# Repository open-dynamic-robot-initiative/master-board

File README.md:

# master-board
Hardware and Firmware of the Solo Quadruped Master Board.

This board centralises all the sensor and actuator data and provides wired and wireless connection to a realtime computer.

Connectivity:

* SPI: Address up to 8 SPI Slave: (max 80Mhz, DMA capable) compatible with BLMC µDriver SPI interface
* Wifi: Wireless communication with a computer via raw ESP-NOW: round trip time of 1.2ms (including driver and OS latency) for a 127bytes message.
* Ethernet: Wired communication with a computer via raw frames: round trip time of 0.2ms (including driver and OS latency) for a 127bytes message.
* GPIO: 4GPIO free. Can be mapped to I2C, UART etc.. Two of them are curently used for IMU communication via UART
* UART: Used to upgrade the ESP32 firmware, free on normal operation.

The board is programed via the ESP-IDF tool chain https://github.com/espressif/esp-idf

Wireless closed loop control at 1kHz demo (click to see video):

IMU, ethernet closed loop cntrol at 1kHz demo (click to see video):

## LED status
**Red fade:** Waiting for init<br>
**Magenta fade:** SPI Autodetect<br>
**Blue fade:** waiting for first commmand<br>
**Green fade:** Active control<br>
**Yellow blink:** ethernet link down state awaiting for link up<br>
**Red blink:** error state (communication with PC), awaiting for new init msg<br>
**White blink:** state machine error (should never happen)<br>

Documentation
-------------
Here are some helpful links to the documentation :

[How to Flash the Master Board (install esp-idf and flash the firmware)](firmware/README.md)

[SDK : How to Prepare Your Interface and Run the Example](sdk/master_board_sdk/README.md)

[Master Board State Machine Description](documentation/masterboard_state_machine.md)

[Description of the Communication Between the Master Board and the Computer](documentation/masterboard_communication.md)

[Description of the BLMC µDriver SPI Interface](documentation/BLMC_%C2%B5Driver_SPI_interface.md)

[Wiring the Master Board](documentation/masterboard_wiring.md)

[Master Board Ordering and Preparation](documentation/masterboard_ordering_soldering.md)

Authors
--------
Thomas Flayols  
Etienne Arlaud

License
-------
BSD 2-Clause License

Copyright
-----------
Copyright (c) 2019, LAAS-CNRS, Max Planck Gesellschaft, New York University

More Information
----------------
[Open Dynamic Robot Initiative](https://open-dynamic-robot-initiative.github.io)

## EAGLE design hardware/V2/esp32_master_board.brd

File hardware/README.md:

The hardware CAD file of the master-board has been created with Eagle.

# Version 1.0 (legacy)
The version 1.0 include an esp32 with GPIO connectors, 8 multiplexed SPI lines, A 5-60V to 3.3V regulator and a Ethernet PHY.
This version suffer from some limitations:
 * The 300ma current limitation of the voltage regulator is easely reach. 
 * The decoupling cappacitor could be increased.
 * The 1st pin label of DEMUX footprint is wrong
 
# Vesrion 2.0 (Latest stable version)
Chage log:
 * Add a RGB LED to ease the feedback while developping.
 * make a dedicated IMU connector
 * Switch to a more capable 3.3V voltage regulator (1A) to power 3DM-CX5-25 IMU

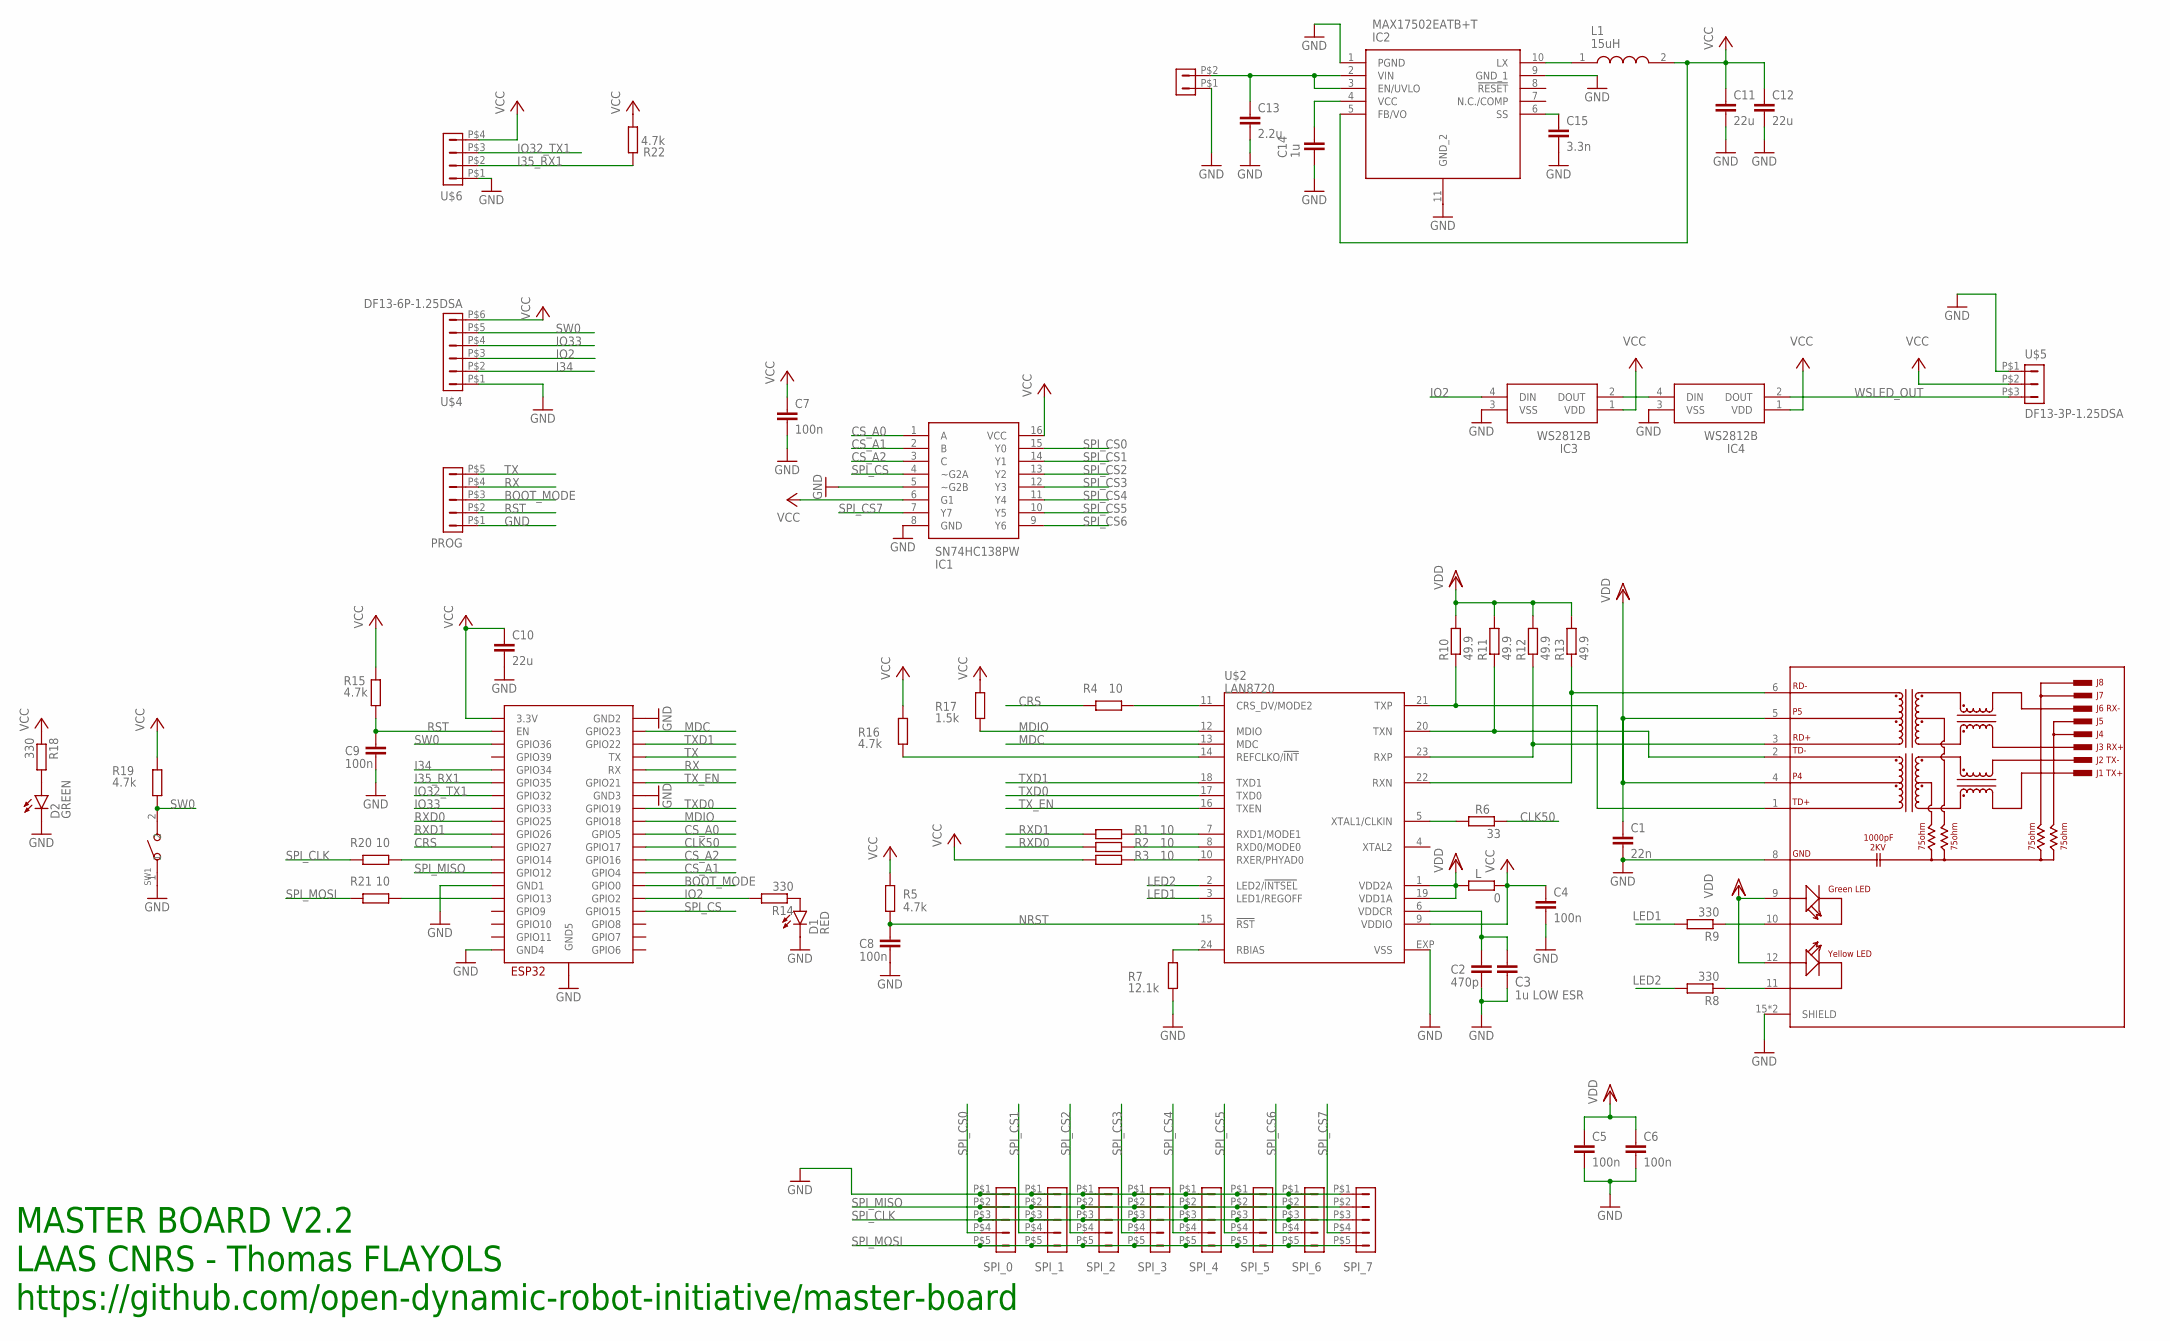
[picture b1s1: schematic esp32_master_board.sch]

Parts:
C1: 22n; 0402; MANUFACTURER_PART_NUMBER 885012205052
C2: 470p; 0402; MANUFACTURER_PART_NUMBER CL05C471JB5NNNC
C3: 1u LOW ESR; 0402; MANUFACTURER_PART_NUMBER CPL-CAP-X5R-0402-1UF-6.3V
C4, C5, C6, C7, C8, C9: 100n; 0402; MANUFACTURER_PART_NUMBER CPL-CAP-X7R-0402-100NF-16V
C10, C11, C12: 22u; C0805; MANUFACTURER_PART_NUMBER CPL-CAP-X5R-0805-22UF-6.3V
C13: 2.2u; C1210; MANUFACTURER_PART_NUMBER C3225X7R1H225K250AB
C14: 1u; 0402; MANUFACTURER_PART_NUMBER CPL-CAP-X5R-0402-1UF-6.3V
C15: 3.3n; 0402; MANUFACTURER_PART_NUMBER 885012205064
D1: RED; CHIPLED_0603; MANUFACTURER_PART_NUMBER CPL-LED-0603-RED
D2: GREEN; CHIPLED_0603; MANUFACTURER_PART_NUMBER CPL-LED-0603-GREEN
IC1: SN74HC138PW; SOP65P640X120-16N
IC2: MAX17502EATB+T; SON50P200X300X80-11N
IC3, IC4: WS2812B
L: 0; 0402; MANUFACTURER_PART_NUMBER CPL-RES-0402-0-0.063W
L1: 15uH; LPS6235
POWER: DF13-2P-1.25DSA; MANUFACTURER_PART_NUMBER DF13-3P-1.25DSA
PROG: DF13-5P-1.25DSA; MANUFACTURER_PART_NUMBER DF13-5P-1.25DSA
R1, R2, R3, R4, R20, R21: 10; 0402; MANUFACTURER_PART_NUMBER CPL-RES-0402-10-0.063W
R5, R15, R16, R19, R22: 4.7k; 0402; MANUFACTURER_PART_NUMBER CPL-RES-0402-4.7K-0.063W
R6: 33; 0402; MANUFACTURER_PART_NUMBER CRCW040233R0FKEDC
R7: 12.1k; 0402; MANUFACTURER_PART_NUMBER ERJ-U02F1212X
R8, R9, R14, R18: 330; 0402; MANUFACTURER_PART_NUMBER RC0402JR-13330RL
R10, R11, R12, R13: 49.9; 0402; MANUFACTURER_PART_NUMBER CRCW040249R9FKEDC
R17: 1.5k; 0402; MANUFACTURER_PART_NUMBER ERJ2GEJ152X
SPI_0, SPI_1, SPI_2, SPI_3, SPI_4, SPI_5, SPI_6, SPI_7: DF13-5P-1.25DSA; MANUFACTURER_PART_NUMBER DF13-5P-1.25DSA
SW1: B3U-1000P-2P-SMD; SW2-2.6-3.0X2.5X1.2+0.4MM; MANUFACTURER_PART_NUMBER B3U-1000P
U$1: ESP32-WROOM; MANUFACTURER_PART_NUMBER ESP32-WROOM-32D
U$2: LAN8720; QFN24; MANUFACTURER_PART_NUMBER LAN8720A-CP
U$3: HR911105A; HANRUN_HR911105A; MANUFACTURER_PART_NUMBER HR911105A
U$4: DF13-6P-1.25DSA; MANUFACTURER_PART_NUMBER DF13-6P-1.25DSA
U$5: DF13-3P-1.25DSA; MANUFACTURER_PART_NUMBER DF13-3P-1.25DSA
U$6: DF13-4P-1.25DSA; MANUFACTURER_PART_NUMBER DF13-4P-1.25DSA

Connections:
BOOT_MODE: PROG.P$3 (3), U$1.IO0 (GPIO0)
CLK50: R6.1, U$1.IO17 (GPIO17)
CRS: R4.1, U$1.IO27 (GPIO27)
CS_A0: IC1.1 (A), U$1.IO5 (GPIO5)
CS_A1: IC1.2 (B), U$1.IO4 (GPIO4)
CS_A2: IC1.3 (C), U$1.IO16 (GPIO16)
GND: C1.2, C2.2, C3.2, C4.2, C5.2, C6.2, C7.2, C8.2, C9.2, C10.2, C11.2, C12.2, C13.2, C14.1, C15.2, D1.C, D2.C, IC1.5 (~G2B), IC1.8 (GND), IC2.1 (PGND), IC2.9 (GND_1), IC2.11 (GND_2), IC3.3 (VSS), IC4.3 (VSS), POWER.P$1 (1), PROG.P$1 (1), R7.1, SPI_0.P$1 (1), SPI_1.P$1 (1), SPI_2.P$1 (1), SPI_3.P$1 (1), SPI_4.P$1 (1), SPI_5.P$1 (1), SPI_6.P$1 (1), SPI_7.P$1 (1), SW1.1, U$1.GND1, U$1.GND2, U$1.GND3, U$1.GND4, U$1.GND5, U$2.EXP (VSS), U$3.8 (GND), U$3.15 (SHIELD), U$3.16 (SHIELD), U$4.P$1 (1), U$5.P$1 (1), U$6.P$1 (1)
I34: U$1.IO34 (GPIO34), U$4.P$2 (2)
I35_RX1: R22.2, U$1.IO35 (GPIO35), U$6.P$2 (2)
IO2: IC3.4 (DIN), R14.2, U$1.IO2 (GPIO2), U$4.P$3 (3)
IO32_TX1: U$1.IO32 (GPIO32), U$6.P$3 (3)
IO33: U$1.IO33 (GPIO33), U$4.P$4 (4)
LED1: R9.2, U$2.3 (LED1/REGOFF)
LED2: R8.2, U$2.2 (LED2/!INTSEL)
MDC: U$1.IO23 (GPIO23), U$2.13 (MDC)
MDIO: R17.1, U$1.IO18 (GPIO18), U$2.12 (MDIO)
unnamed: R1.2, U$2.7 (RXD1/MODE1)
unnamed: R2.2, U$2.8 (RXD0/MODE0)
unnamed: R3.2, U$2.10 (RXER/PHYAD0)
unnamed: R4.2, U$2.11 (CRS_DV/MODE2)
unnamed: R6.2, U$2.5 (XTAL1/CLKIN)
unnamed: R7.2, U$2.24 (RBIAS)
unnamed: R10.1, U$2.21 (TXP), U$3.1 (TD+)
unnamed: R11.1, U$2.20 (TXN), U$3.2 (TD-)
unnamed: R12.1, U$2.23 (RXP), U$3.3 (RD+)
unnamed: R13.1, U$2.22 (RXN), U$3.6 (RD-)
unnamed: R8.1, U$3.11 (YC)
unnamed: R9.1, U$3.10 (GC)
unnamed: R16.1, U$2.14 (REFCLKO/!INT)
unnamed: C2.1, C3.1, U$2.6 (VDDCR)
unnamed: C14.2, IC2.4 (VCC)
unnamed: D1.A, R14.1
unnamed: R21.2, U$1.IO13 (GPIO13)
unnamed: IC2.10 (LX), L1.1
unnamed: IC3.2 (DOUT), IC4.4 (DIN)
unnamed: D2.A, R18.2
unnamed: R20.2, U$1.IO14 (GPIO14)
unnamed: C15.1, IC2.6 (SS)
unnamed: C13.1, IC2.2 (VIN), IC2.3 (EN/UVLO), POWER.P$2 (2)
NRST: C8.1, R5.1, U$2.15 (!RST)
RST: C9.1, PROG.P$2 (2), R15.1, U$1.EN
RX: PROG.P$4 (4), U$1.RX
RXD0: R2.1, U$1.IO25 (GPIO25)
RXD1: R1.1, U$1.IO26 (GPIO26)
SPI_CLK: R20.1, SPI_0.P$3 (3), SPI_1.P$3 (3), SPI_2.P$3 (3), SPI_3.P$3 (3), SPI_4.P$3 (3), SPI_5.P$3 (3), SPI_6.P$3 (3), SPI_7.P$3 (3)
SPI_CS: IC1.4 (~G2A), U$1.IO15 (GPIO15)
SPI_CS0: IC1.15 (Y0), SPI_0.P$4 (4)
SPI_CS1: IC1.14 (Y1), SPI_1.P$4 (4)
SPI_CS2: IC1.13 (Y2), SPI_2.P$4 (4)
SPI_CS3: IC1.12 (Y3), SPI_3.P$4 (4)
SPI_CS4: IC1.11 (Y4), SPI_4.P$4 (4)
SPI_CS5: IC1.10 (Y5), SPI_5.P$4 (4)
SPI_CS6: IC1.9 (Y6), SPI_6.P$4 (4)
SPI_CS7: IC1.7 (Y7), SPI_7.P$4 (4)
SPI_MISO: SPI_0.P$2 (2), SPI_1.P$2 (2), SPI_2.P$2 (2), SPI_3.P$2 (2), SPI_4.P$2 (2), SPI_5.P$2 (2), SPI_6.P$2 (2), SPI_7.P$2 (2), U$1.IO12 (GPIO12)
SPI_MOSI: R21.1, SPI_0.P$5 (5), SPI_1.P$5 (5), SPI_2.P$5 (5), SPI_3.P$5 (5), SPI_4.P$5 (5), SPI_5.P$5 (5), SPI_6.P$5 (5), SPI_7.P$5 (5)
SW0: R19.1, SW1.2, U$1.SENSOR_VP (GPIO36), U$4.P$5 (5)
TX: PROG.P$5 (5), U$1.TX
TXD0: U$1.IO19 (GPIO19), U$2.17 (TXD0)
TXD1: U$1.IO22 (GPIO22), U$2.18 (TXD1)
TX_EN: U$1.IO21 (GPIO21), U$2.16 (TXEN)
VCC: C4.1, C7.1, C10.1, C11.1, C12.1, IC1.6 (G1), IC1.16 (VCC), IC2.5 (FB/VO), IC3.1 (VDD), IC4.1 (VDD), L.1, L1.2, R3.1, R5.2, R15.2, R16.2, R17.2, R18.1, R19.2, R22.1, U$1.3V3 (3.3V), U$2.9 (VDDIO), U$4.P$6 (6), U$5.P$2 (2), U$6.P$4 (4)
VDD: C1.1, C5.1, C6.1, L.2, R10.2, R11.2, R12.2, R13.2, U$2.1 (VDD2A), U$2.19 (VDD1A), U$3.4, U$3.5, U$3.9 (GA), U$3.12 (YA)
WSLED_OUT: IC4.2 (DOUT), U$5.P$3 (3)

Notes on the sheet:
MASTER BOARD V2.2 LAAS CNRS - Thomas FLAYOLS https://github.com/open-dynamic-robot-initiative/master-board

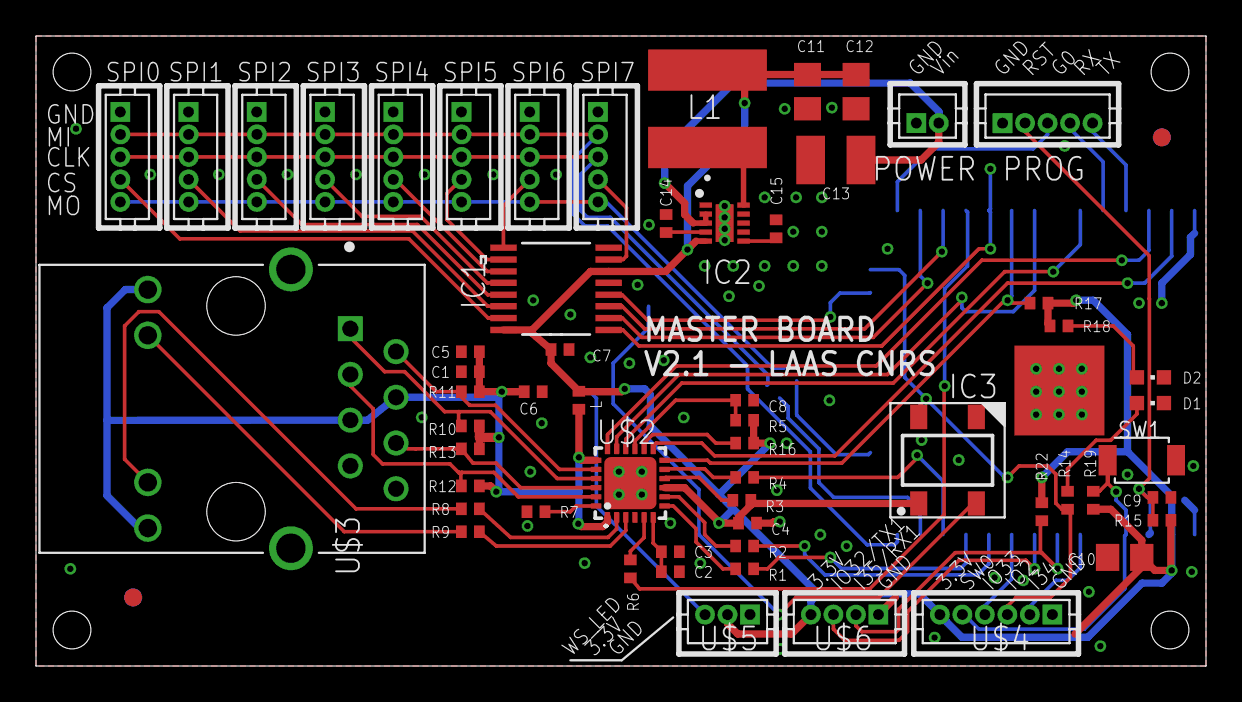
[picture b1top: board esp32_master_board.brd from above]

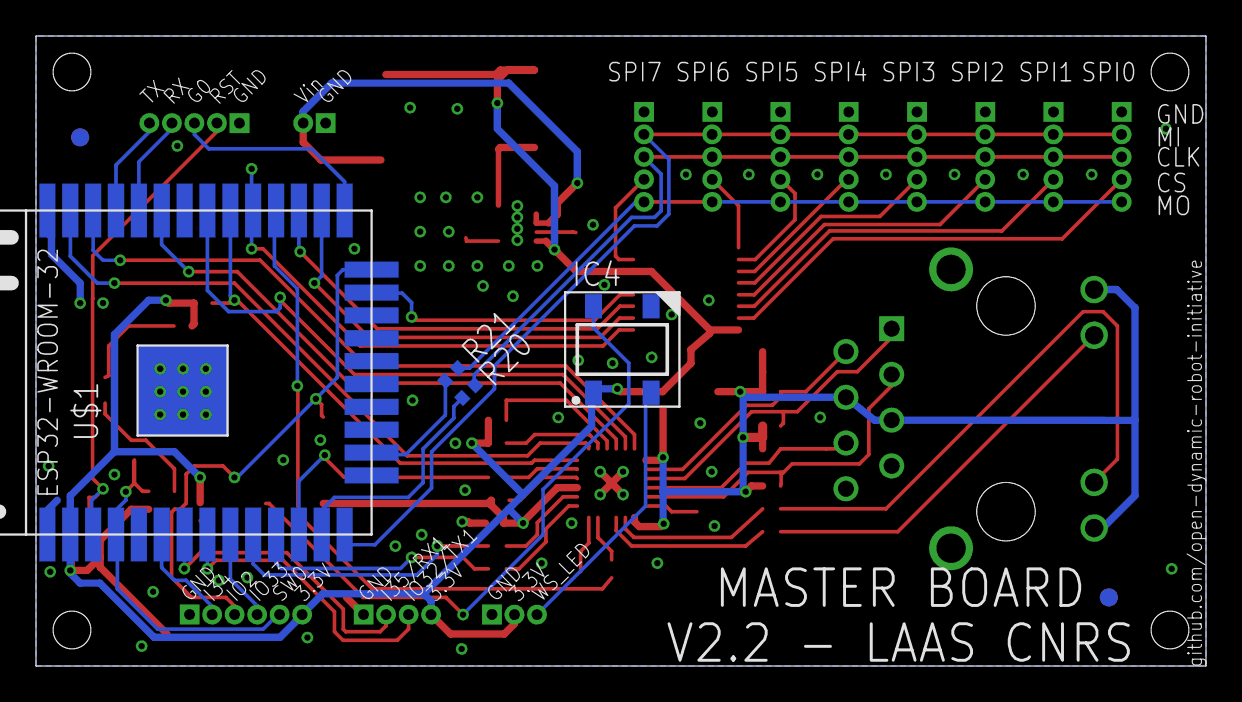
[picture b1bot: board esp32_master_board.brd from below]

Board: 2 copper layers, 65.0 x 35.0 mm, 66 parts (6 on the bottom side), 64 nets.

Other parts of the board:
REF1, REF2, REF3, REF4: VISION_REF10

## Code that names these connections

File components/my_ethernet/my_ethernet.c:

#include "my_ethernet.h"

uint8_t eth_src_mac[6] = {0xb4, 0xe6, 0x2d, 0xb5, 0x9f, 0x88};
uint8_t eth_dst_mac[6] = {0xFF, 0xFF, 0xFF, 0xFF, 0xFF, 0xFF};

void (*eth_recv_cb)(uint8_t src_mac[6], uint8_t *data, int len) = NULL;

static const char* ETH_TAG = "my_ethernet";

static void eth_gpio_config_rmii(void) {
    // RMII data pins are fixed:
    // TXD0 = GPIO19
    // TXD1 = GPIO22
    // TX_EN = GPIO21
    // RXD0 = GPIO25
    // RXD1 = GPIO26
    // CLK == GPIO0
    phy_rmii_configure_data_interface_pins();
    phy_rmii_smi_configure_pins(PIN_SMI_MDC, PIN_SMI_MDIO);
}


static esp_err_t eth_event_handler(void *ctx, system_event_t *event) {
  tcpip_adapter_ip_info_t ipInfo;

  switch(event->event_id) {
    case ETHERNET_EVENT_CONNECTED:
        ESP_LOGI(ETH_TAG, "Ethernet Link Up");
        break;
    case ETHERNET_EVENT_DISCONNECTED:
        ESP_LOGI(ETH_TAG, "Ethernet Link Down");
        break;
    case ETHERNET_EVENT_START:
        ESP_LOGI(ETH_TAG, "Ethernet Started");
        break;
    case ETHERNET_EVENT_STOP:
        ESP_LOGI(ETH_TAG, "Ethernet Stopped");
        break;
    case SYSTEM_EVENT_ETH_GOT_IP:
        ESP_LOGI(ETH_TAG, "Ethernet got IP");
        ESP_ERROR_CHECK(tcpip_adapter_get_ip_info(TCPIP_ADAPTER_IF_ETH, &ipInfo));
        ESP_LOGI(ETH_TAG, "TCP/IP initialization finished.");
        ESP_LOGI(ETH_TAG, "TCP|IP \t IP:"IPSTR, IP2STR(&ipInfo.ip));
        ESP_LOGI(ETH_TAG, "TCP|IP \t MASK:"IPSTR, IP2STR(&ipInfo.netmask));
        ESP_LOGI(ETH_TAG, "TCP|IP \t GW:"IPSTR, IP2STR(&ipInfo.gw));
        xEventGroupSetBits(udp_event_group, WIFI_CONNECTED_BIT);
    default:
      ESP_LOGI(ETH_TAG, "Unhandled Ethernet event (id = %d)", event->event_id);
        break;
    }
  return ESP_OK;
}


static esp_err_t eth_recv_func (void *buffer, uint16_t len, void *eb) {
  eth_frame *frame = buffer;
  if(eth_recv_cb == NULL) {
    ESP_LOGE(ETH_TAG, "Ethernet frame received but no callback function is set on received...");
  } else if(len < sizeof(eth_frame) - CONFIG_MAX_ETH_DATA_LEN) {
    ESP_LOGE(ETH_TAG, "The ethernet frame received is too short : frame length = %dB / minimum length expected (for header) = %dB", len, sizeof(eth_frame) - CONFIG_MAX_ETH_DATA_LEN);
  } else if(len > sizeof(eth_frame)) {
    ESP_LOGE(ETH_TAG, "The ethernet frame received is too long : frame length = %dB / maximum length = %dB", len, sizeof(eth_frame));
  } else if(frame->ethertype != ETHERTYPE) {
    ESP_LOGE(ETH_TAG, "Unexpected frame ethertype : got %d instead of %d", frame->ethertype, ETHERTYPE);
  } else if(frame->data_len > len - sizeof(eth_frame) + CONFIG_MAX_ETH_DATA_LEN) {
    ESP_LOGE(ETH_TAG, "Data longer than available frame length : data length = %d / available frame length = %d", frame->data_len, len - sizeof(eth_frame) + CONFIG_MAX_ETH_DATA_LEN);
  } else {
    eth_recv_cb(frame->dst_mac, frame->data, frame->data_len);
  }
  return ESP_OK;
}


void eth_init_frame(eth_frame *p_frame) {
  p_frame->ethertype = ETHERTYPE;
  memcpy(p_frame->dst_mac, eth_dst_mac, sizeof(uint8_t) * 6);  
  memcpy(p_frame->src_mac, eth_src_mac, sizeof(uint8_t) * 6);
}


esp_err_t eth_send_frame(eth_frame *p_frame)
{
  int err = esp_eth_tx((uint8_t *) p_frame, sizeof(eth_frame) + (p_frame->data_len) - CONFIG_MAX_ETH_DATA_LEN);
  
  if (err < 0) {
    ESP_LOGE(ETH_TAG, "Erromar occurred while sending eth frame: errno %d", errno);
    return ESP_FAIL;
  }

  return ESP_OK;
}


void eth_detach_recv_cb() {
  eth_recv_cb = NULL;
}


void eth_attach_recv_cb(void (*cb)(uint8_t src_mac[6], uint8_t *data, int len)) {
  eth_recv_cb = cb;
}


void eth_init() {
  ////////////////////////////////////
  //EVENT HANDLER (CALLBACK)
  ////////////////////////////////////
    //TCP/IP event handling & group (akin to flags and semaphores)
    udp_event_group = xEventGroupCreate();
    ESP_ERROR_CHECK(esp_event_loop_init(eth_event_handler, NULL) );

  ////////////////////////////////////
  //TCP/IP DRIVER INIT WITH A STATIC IP
  ////////////////////////////////////
    tcpip_adapter_init();
    tcpip_adapter_ip_info_t ipInfo;

    //Stop DHCP
    tcpip_adapter_dhcpc_stop(TCPIP_ADAPTER_IF_ETH);

    //Set the static IP
    ip4addr_aton(DEVICE_IP, &ipInfo.ip);
    ip4addr_aton(DEVICE_GW, &ipInfo.gw);
    ip4addr_aton(DEVICE_NETMASK, &ipInfo.netmask);
    ESP_ERROR_CHECK(tcpip_adapter_set_ip_info(TCPIP_ADAPTER_IF_ETH, &ipInfo));

  ////////////////////////////////////
  //ETHERNET CONFIGURATION & INIT
  ////////////////////////////////////

    eth_config_t config = ETHERNET_PHY_CONFIG;
    config.phy_addr = PHY1;
    config.gpio_config = eth_gpio_config_rmii;
    config.tcpip_input = &eth_recv_func;
    config.clock_mode = CONFIG_PHY_CLOCK_MODE;

    ESP_ERROR_CHECK(esp_eth_init(&config));
    ESP_ERROR_CHECK(esp_eth_enable());

    ESP_LOGI(ETH_TAG, "Establishing connetion...");
    xEventGroupWaitBits(udp_event_group, WIFI_CONNECTED_BIT,true, true, portMAX_DELAY);
    ESP_LOGI(ETH_TAG, "Connected");
}

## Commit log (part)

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2020-03-30 add feedback on packet loss
2020-03-30 Add link to the wiring documentation
2020-04-02 New ethernet lib to work with ESP-IDF v4.0
2020-04-04 New sdkconfig to work with ESP-IDF v4.0 (generated from .defaults)
2020-04-04 Update .gitignore for current sdk location
2020-04-05 Fix wrong variable name
2020-04-07 Remove button handling
2020-04-07 Giving feedback on packet loss
2020-04-07 Handling the case when no link state callback function has been set
2020-04-08 Update master board state diagram image
2020-04-14 Initializing p_trans array to avoid a very rare and specific crash while sending an init msg to the mb
2020-04-14 Small refactor + a few comments
2020-04-15 Reset variables for feedback on packet loss after init
2020-04-15 Lttle fix on copying state in main callback
2020-04-16 Small refactor spi_autodetect state
2020-04-16 Added feedback on number of spi slaves connected in ack msg
2020-04-16 Update documentation for feedback on connected SPI slaves
2020-04-17 Updated documentation with protocol version in init msgs
2020-04-17 Added an error msg to sensor packet when a spi transaction failed
2020-04-17 Better handling of variables when there is a state change
2020-04-17 Added listener mode to the interface that allows to get sensor data from any running mb (no session id checking)
2020-04-20 Added getters for feedback and changed stats print functions
2020-04-21 Initialization of bpf in ESPNOW_manager
2020-04-21 Update doc about session id
2020-04-23 Updated outdated doc
2020-04-28 Added default argument for listener mode in interface constructor
2020-05-04 Close correctly the pthread to avoid memory leaks
2020-05-04 Free link_handler when the program is stopped by SIGINT signal
2020-05-04 Disabled debug prints
2020-05-07 Fix for command loss feedback reset and overflow
2020-05-09 [hardware] V2.1: Add MPN for all parts, fix some footprints, add BOM compatible with seeedfusion PCBA, add pick and place files
2020-05-12 Small trace path changes to prevent possible shorting of MISO line due to sharp grounded ESP32 module corner, small optimisations
2020-05-15 Removed mistakenly added line in default config
2020-05-20 Documentation update : added informations about the latency calculator script
2020-06-11 Improving display of latency test result
2020-06-12 Revert "Changing scheduler param to realtime in examples"
    This reverts commit beead35848bc759a2ef147b0a68dc79b47e57f74.
2020-06-17 Merged PrintCmdStats and PrintSensorStats, improved the display of wifi/eth stats
2020-06-24 Added getters for wifi channel and protocol version
2020-07-06 Update state machine documentation
2020-07-07 Removed wifi channel menuconfig entry and tcpip adpater use
2020-07-07 Fixed wifi deinit and channel change issue
2020-07-15 Small fix for wifi event handlers
2020-07-16 SPI: using polling instead of interrupts
2020-07-16 Placed spi pre and post cbs into IRAM
2020-07-21 Plot graphs even if the script is stopped by a master board timeout
2020-07-31 Temporary fix failing spi transactions in error state
2020-07-31 Update sdkconfig
2020-08-26 Update WS2812b library to remove ambiguity on the part orientation (pin3 indicated by a triangle on the part)
2020-10-07 Tune data representation in the protocol for usefull gains levels, Fix conevrsion of Kp Kd
2020-10-13 CMake: ensure python lib always find c++ lib
2020-11-13 [SDK] Add support for current saturation
2020-11-16 export the cmake library
2020-11-16 Synchronize.
2020-11-16 fix a couple of warnings
2020-11-17 update the interface to double values
2020-12-01 SDK: Adding error code for encoder2 error
2021-01-20 Revert the change for CONFIG_SPI_N_ATTEMPT 3 -> 2
2021-02-24 added led status at readme
2021-04-13 [firmware] update doc
2021-06-25 Set close to zero velocity to zero. Fixes #92
2021-07-13 Fix problem with reference to packed fields in MasterBoardInterface::ParseSensorData
2021-07-21 Add comment to explain the call to ParseSensorData
2021-07-28 update doc including powerboard data in sensor packets
2021-08-02 Implement changes to protocol #4 for the feedforward profile in the SDK and firmware
2021-09-23 pull out more data
2021-10-05 print the histogram and dumpt data all the time
2021-10-18 fix "cannot bind packed field" on Ubuntu 20.04
    While the old version is building on Ubuntu 18.04, newer versions of gcc
    do not allow the assignment to reference here.
2022-01-21 SDK: cherry-pick fixes, fix #106
    initial commit: 32b0252c64a064c55e8cd07115a003b15c0d0a86
2022-03-16 Update README.md
    Fix License according to License file
2022-04-08 Rewrite IMU driver using mailbox, fixing esp32 hardware bug on uart fifo
2022-05-20 Adding example for collecting and plotting IMU data for 10 seconds
2022-05-23 fix example_imu_data_collection
2022-07-19 1. implemented substitution clock() to perf_counter because of python3 don't maintain already it. 2. in line while ((not robot_if.IsTimeout()) and ( (perf_counter() - glob_last) < 20)): created misse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
2022-09-16 Avoid fixed-point overflow
2022-09-19 Increase FLOAT_TO_D32QN &c range
2022-09-20 Check for compatible catch2 version
2022-09-28 Revert "Add error code for SPI CRC error"
    This reverts commit 5d95db4b35e33a5f52f3c232c0c7dbf1ebddd7ec.
2022-09-28 Handle out-of-range motor params without wraparound (#117)
    Avoid fixed-point overflow
2022-12-21 Remove vscode hidden files
2022-12-22 plateform and distro modules optionnal for sdk example com_analyser.py
2023-01-31 fixed typos in firmware README.md
2023-03-08 Zero-initialise all members of Motor
    This should fix an issue that was likely caused by `kp` being set to
    some random non-zero value, resulting in the motor unintentionally being
    held at some position.
2023-03-08 example.py: Initialise all reference values and gains to zero
    This should not really be needed anymore since values are already
    zero-initialised in `Motor` but better be safe than sorry.
2023-03-11 Fix missing header.
2023-04-17 [Link_manager] Fix message when the priority is not set correctly and fails using assert.
2023-04-25 pre-commit
2023-05-26 Add .github/workflows
2023-05-26 [package.xml] XML version 1.0
2023-05-27 [Cmake] remove python components.
2023-05-29 [sdk/master_board_sdk/CMakeLists.txt] Update Find Python detection. Update message when detection is failing.
2023-05-29 [cmake] Change again python detection place.
2023-05-29 [github/workflows/ros-ci.yml] Fix wrong directory.
2023-06-21 [cmake] Add install procedure for file package.xml
2023-06-23 [CMakeLists.txt] Uses ROS-2 if the environment is compatible.
2023-06-23 [master_board_sdk/package.xml] Remove ament_cmake dependency and buildtool dependency.
2023-07-10 Bump ros-industrial/industrial_ci
    Bumps [ros-industrial/industrial_ci](https://github.com/ros-industrial/industrial_ci) from afbf77f39db26785371161d5691ab435b31bb3ba to 9f963f67ebb889792175776c5ee00134d7bb569b.
    - [Commits](https://github.com/ros-industrial/industrial_ci/compare/afbf77f39db26785371161d5691ab435b31bb3ba...9f963f67ebb889792175776c5ee00134d7bb569b)
    ---
    updated-dependencies:
    - dependency-name: ros-industrial/industrial_ci
    dependency-type: direct:production
2023-09-04 Bump actions/checkout from 3 to 4
    Bumps [actions/checkout](https://github.com/actions/checkout) from 3 to 4.
    - [Release notes](https://github.com/actions/checkout/releases)
    - [Changelog](https://github.com/actions/checkout/blob/main/CHANGELOG.md)
    - [Commits](https://github.com/actions/checkout/compare/v3...v4)
    ---
    updated-dependencies:
2023-09-05 [protocol] FLOAT_TO_D8QN has a wrong bracket. This commit fix this.
2023-09-25 CMake: get the submodule if necessary
2023-10-11 Fix git conflicts
2023-11-27 Bump ros-industrial/industrial_ci
    Bumps [ros-industrial/industrial_ci](https://github.com/ros-industrial/industrial_ci) from 9e8b4aaec69f7cade96eda5cfcb3e7da57b99c6e to 3ed9846c96ed1e0bb36193e8e250632eaac980d0.
    - [Commits](https://github.com/ros-industrial/industrial_ci/compare/9e8b4aaec69f7cade96eda5cfcb3e7da57b99c6e...3ed9846c96ed1e0bb36193e8e250632eaac980d0)
    ---
    updated-dependencies:
    - dependency-name: ros-industrial/industrial_ci
    dependency-type: direct:production
2024-01-22 Bump actions/cache from 3 to 4
    Bumps [actions/cache](https://github.com/actions/cache) from 3 to 4.
    - [Release notes](https://github.com/actions/cache/releases)
    - [Changelog](https://github.com/actions/cache/blob/main/RELEASES.md)
    - [Commits](https://github.com/actions/cache/compare/v3...v4)
    ---
    updated-dependencies:
2024-03-31 Add stdexcept as an include in example.cpp Fix https://github.com/open-dynamic-robot-initiative/master-board/issues/153
2024-04-04 Add CV7-AHRS IMU and selection menu
2024-05-04 Add missing stdexcept.
2024-05-17 CMakeLists.txt : don't search for boost.python, let the jrl cmakemodule do the job
2024-06-21 [tests] Add dependency to catch2 for tests in package.xml
2024-06-21 [github/workflows] Renamed correctly the workflows.
2024-06-28 Fix CHANGELOG.md for the given
2024-07-05 CMake: we need to search for boost python if we want to link to it
2025-05-20 Cmake: update submodule
2025-05-21 nix: add flake for sdk package
2025-05-21 ci: checking out the code helps, usually
2025-05-21 nix: preemptively add python312Packages.numpy as runtime dep
2025-05-21 Revert "ci debug why submodules: recursive does nothing"
    This reverts commit 3f6f59a384defbc28bf7bc6c60c076b7fd89eea2.
2025-05-21 ci: enable logs for nix build
2025-05-21 nix: dynamically get ROS version from package.xml
    see https://github.com/Gepetto/nix-lib/pull/1
2025-05-22 ci: enforce flake.lock correctness
2025-05-26 ci: debug missig arg src-*
2025-06-02 nix: fix rosVersion call, add example/ to src fileset
2025-06-03 typo
2025-06-04 ci: run on macos too
2025-06-05 fix formatting blunder
2025-08-19 Bump actions/checkout from 4 to 5
    Bumps [actions/checkout](https://github.com/actions/checkout) from 4 to 5.
    - [Release notes](https://github.com/actions/checkout/releases)
    - [Changelog](https://github.com/actions/checkout/blob/main/CHANGELOG.md)
    - [Commits](https://github.com/actions/checkout/compare/v4...v5)
    ---
    updated-dependencies:
2025-12-15 Bump ros-industrial/industrial_ci
    Bumps [ros-industrial/industrial_ci](https://github.com/ros-industrial/industrial_ci) from eb3ea328ff056aa2435d5b3493e7e2929c310f8e to ba2a3d0f830f8051b356711a8df2fedfc5d256cf.
    - [Commits](https://github.com/ros-industrial/industrial_ci/compare/eb3ea328ff056aa2435d5b3493e7e2929c310f8e...ba2a3d0f830f8051b356711a8df2fedfc5d256cf)
    ---
    updated-dependencies:
    - dependency-name: ros-industrial/industrial_ci
    dependency-version: ba2a3d0f830f8051b356711a8df2fedfc5d256cf

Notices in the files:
parts and their libraries:
microchip-smsc-lan8720: (C) 2014 Tomasz Boleslaw CEDRO, cederom@tlen.pl, http://www.tomek.cedro.info.
dicons: Copyright (C) 2004, Bob Starr (rtzaudio@mindspring.com)
